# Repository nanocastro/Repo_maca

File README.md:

# Hemos trasladado el repositorio a https://gitlab.com/nanocastro/Repo_maca
# MACA
## Monitor Abierto de Calidad de Aire

**Prototipo desarrollado por el Laboratorio de Análisis Quimico y Laboratorio de Análisis Instrumental de la DETI
Facultad de Ingeniería - Universidad Nacional de Cuyo**

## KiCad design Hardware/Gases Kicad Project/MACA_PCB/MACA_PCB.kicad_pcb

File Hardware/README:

# README
Please refer to "MACA PCB Description.pdf" file when assembly.
There are two wired jumpers marked (with red circles and lines) that connect the voltage supply net.

For gases concentration measurement:
The latest schematic is the one named "MACA Esquematico.pdf", this schematic has been made in kicad due 
to file corruption of the previous ones (made with proteus). The new pcb board is not yet finished (at 15th May) 
but contains the same circuits and components as the previous PCB.  

For particle measurent:
There is a kicad project for an arduino mega 2560 shield that hosts several particle sensors and logs their measurement: 
 - SDS011 
 - PLantower S7003 
 - Shinyei PPD42

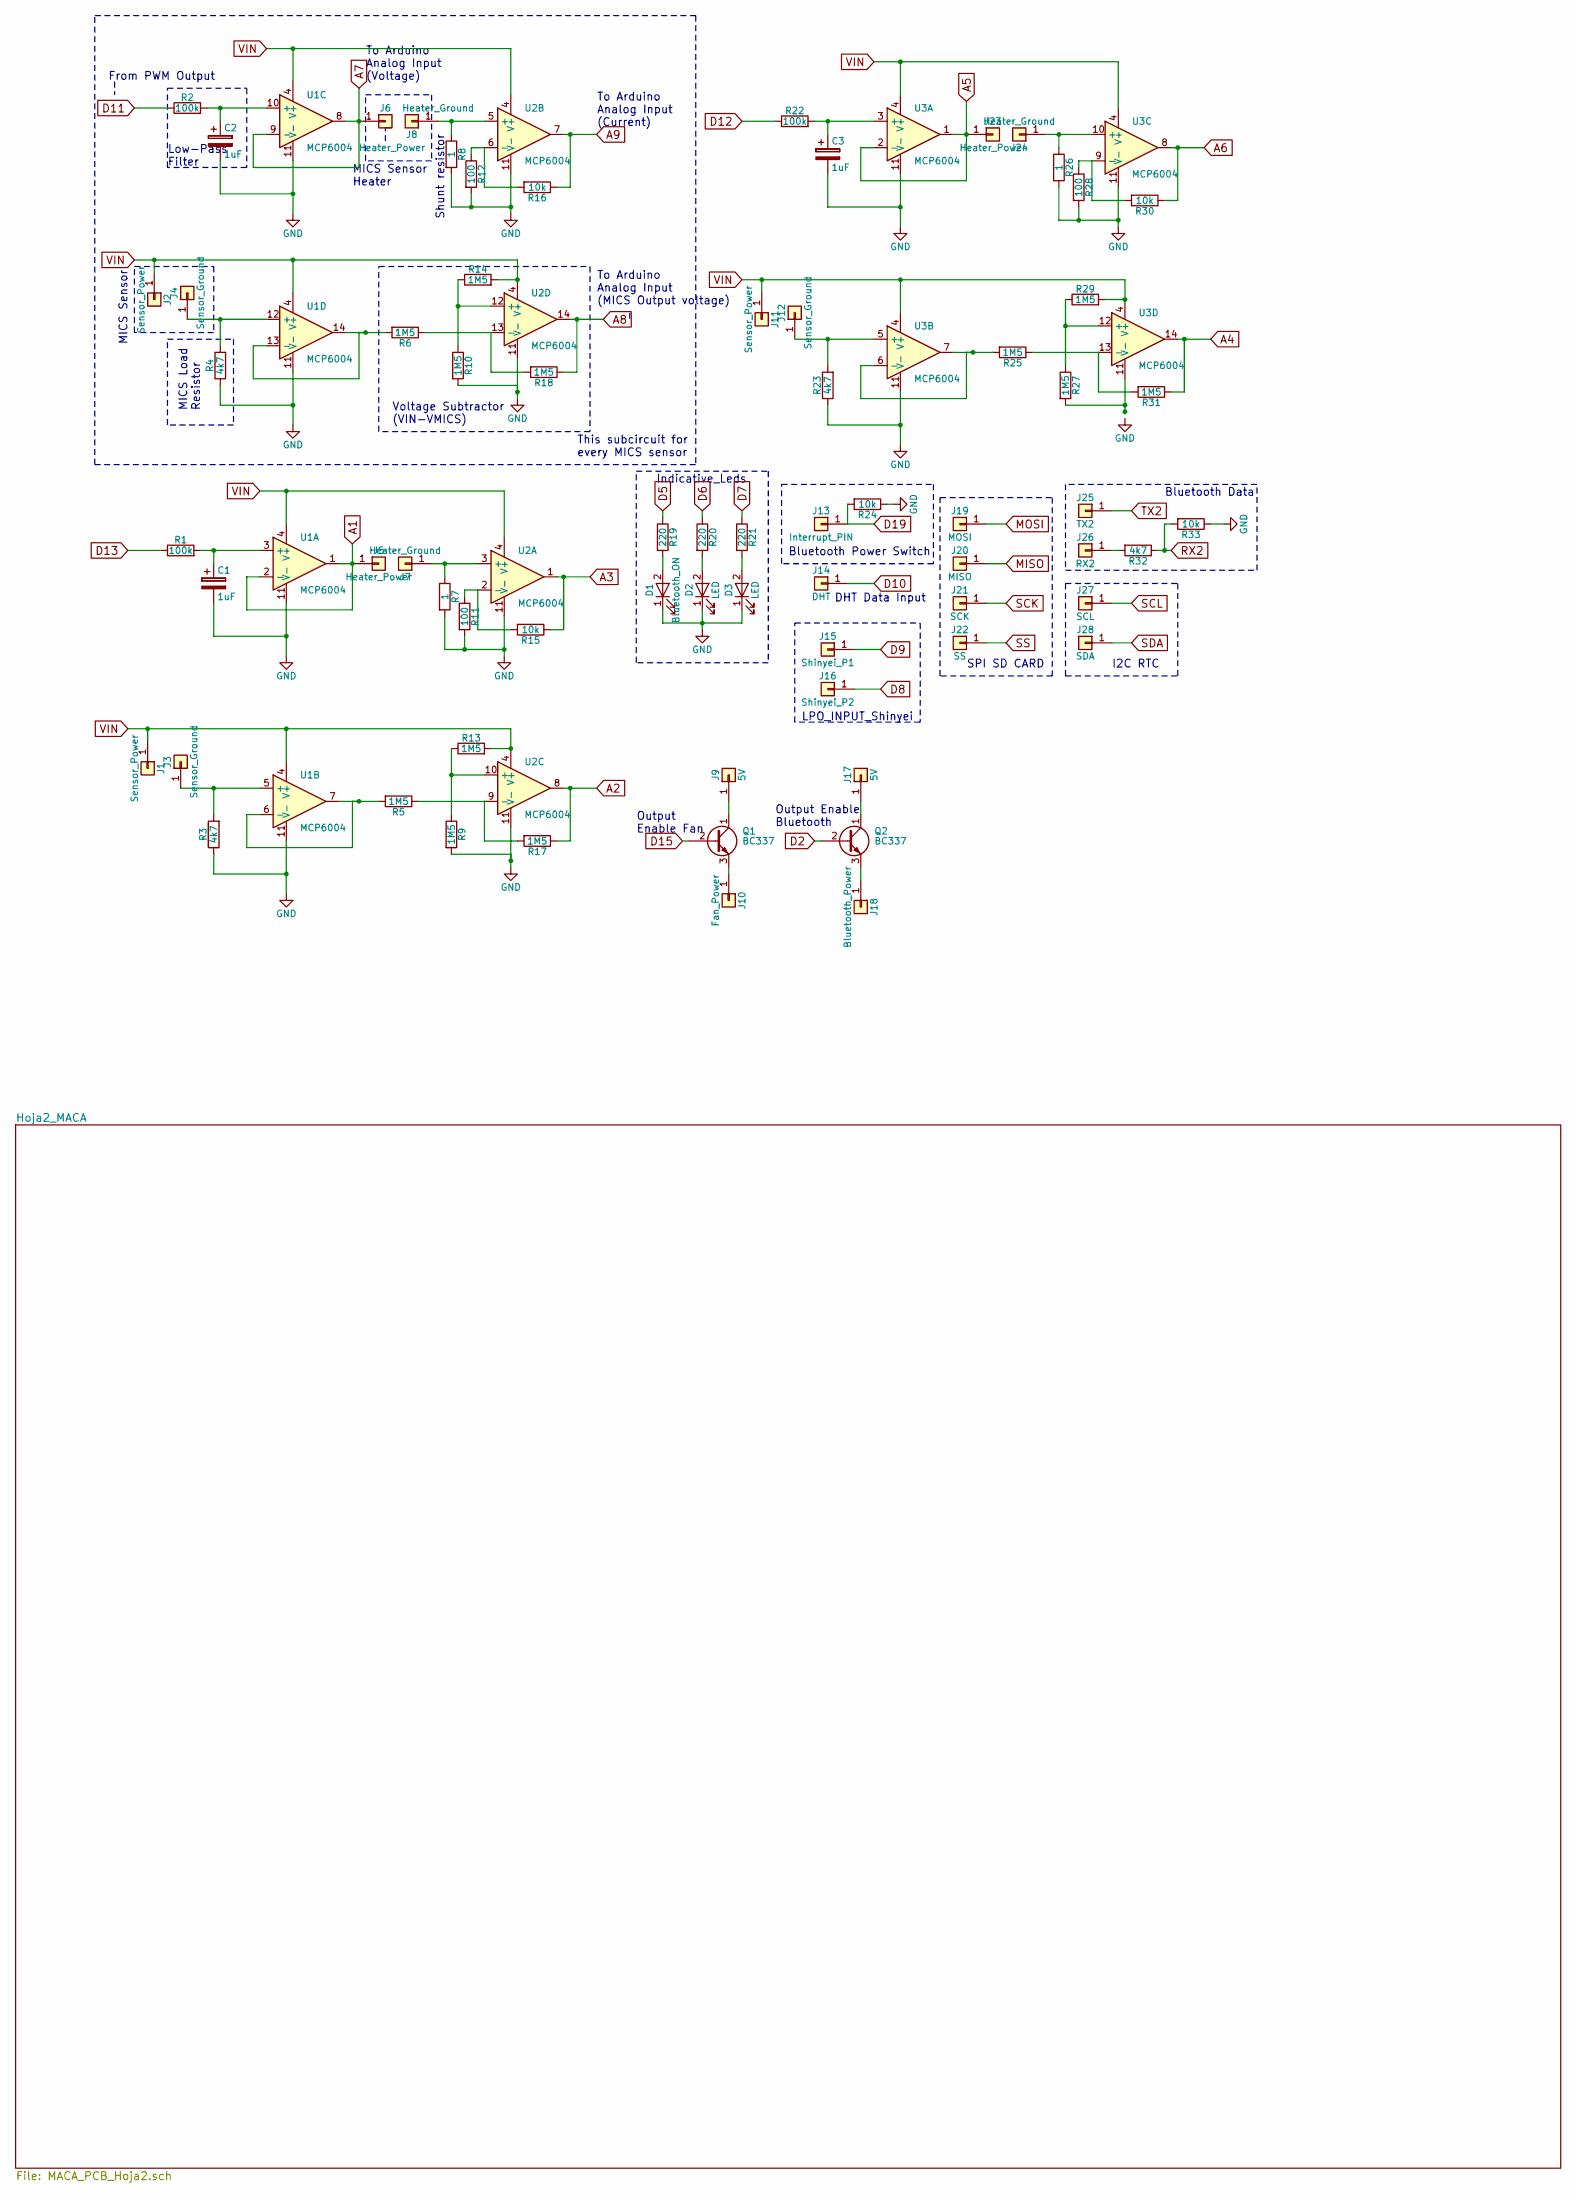
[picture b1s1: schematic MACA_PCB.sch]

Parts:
C1, C2, C3: 1uF; CP_Radial_D5.0mm_P2.50mm
D1: Bluetooth_ON; LED_D5.0mm
D2, D3: LED; LED_D5.0mm
J1, J2, J11: Sensor_Power; Pin_Header_Straight_1x01_Pitch2.54mm
J3, J4, J12: Sensor_Ground; Pin_Header_Straight_1x01_Pitch2.54mm
J5, J6, J23: Heater_Power; Pin_Header_Straight_1x01_Pitch2.54mm
J7, J8, J24: Heater_Ground; Pin_Header_Straight_1x01_Pitch2.54mm
J9, J17: 5V; Pin_Header_Straight_1x01_Pitch2.54mm
J10: Fan_Power; Pin_Header_Straight_1x01_Pitch2.54mm
J13: Interrupt_PIN; Pin_Header_Straight_1x01_Pitch2.54mm
J14: DHT; Pin_Header_Straight_1x01_Pitch2.54mm
J15: Shinyei_P1; Pin_Header_Straight_1x01_Pitch2.54mm
J16: Shinyei_P2; Pin_Header_Straight_1x01_Pitch2.54mm
J18: Bluetooth_Power; Pin_Header_Straight_1x01_Pitch2.54mm
J19: MOSI; Pin_Header_Straight_1x01_Pitch2.54mm
J20: MISO; Pin_Header_Straight_1x01_Pitch2.54mm
J21: SCK; Pin_Header_Straight_1x01_Pitch2.54mm
J22: SS; Pin_Header_Straight_1x01_Pitch2.54mm
J25: TX2; Pin_Header_Straight_1x01_Pitch2.54mm
J26: RX2; Pin_Header_Straight_1x01_Pitch2.54mm
J27: SCL; Pin_Header_Straight_1x01_Pitch2.54mm
J28: SDA; Pin_Header_Straight_1x01_Pitch2.54mm
Q1, Q2: BC337; TO-92_Molded_Narrow
R1, R2, R22: 100k; R_Axial_DIN0204_L3.6mm_D1.6mm_P7.62mm_Horizontal
R3, R4, R23, R32: 4k7; R_Axial_DIN0204_L3.6mm_D1.6mm_P7.62mm_Horizontal
R5, R6, R9, R10, R13, R14, R17, R18, R25, R27, R29, R31: 1M5; R_Axial_DIN0204_L3.6mm_D1.6mm_P7.62mm_Horizontal
R7, R8, R26: 1; R_Axial_DIN0204_L3.6mm_D1.6mm_P7.62mm_Horizontal
R11, R12, R28: 100; R_Axial_DIN0204_L3.6mm_D1.6mm_P7.62mm_Horizontal
R15, R16, R24, R30, R33: 10k; R_Axial_DIN0204_L3.6mm_D1.6mm_P7.62mm_Horizontal
R19, R20, R21: 220; R_Axial_DIN0204_L3.6mm_D1.6mm_P7.62mm_Horizontal
U1, U2, U3: MCP6004; DIP-14_W7.62mm

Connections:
A1: J5.1, U1.1, U1.2 (-); also elsewhere on the board
A3: R15.1, U2.1; also elsewhere on the board
A4: R31.1, U3.14; also elsewhere on the board
A5: J23.1, U3.1, U3.2 (-); also elsewhere on the board
A6: R30.1, U3.8; also elsewhere on the board
A7: J6.1, U1.8, U1.9 (-); also elsewhere on the board
A8: R18.1, U2.14; also elsewhere on the board
A9: R16.1, U2.7; also elsewhere on the board
D2: Q2.2 (B); also elsewhere on the board
D5: R19.1; also elsewhere on the board
D6: R20.1; also elsewhere on the board
D7: R21.1; also elsewhere on the board
D8: J16.1; also elsewhere on the board
D9: J15.1; also elsewhere on the board
D10: J14.1; also elsewhere on the board
D11: R2.1; also elsewhere on the board
D12: R22.1; also elsewhere on the board
D13: R1.1; also elsewhere on the board
D15: Q1.2 (B); also elsewhere on the board
D19: J13.1, R24.2; also elsewhere on the board
MISO: J20.1; also elsewhere on the board
MOSI: J19.1; also elsewhere on the board
unnamed: C1.1, R1.2, U1.3 (+)
unnamed: C2.1, R2.2, U1.10 (+)
unnamed: C3.1, R22.2, U3.3 (+)
unnamed: D1.2 (A), R19.2
unnamed: D2.2 (A), R20.2
unnamed: D3.2 (A), R21.2
unnamed: J3.1, R3.2, U1.5 (+)
unnamed: J4.1, R4.2, U1.12 (+)
unnamed: J7.1, R7.1, U2.3 (+)
unnamed: J8.1, R8.1, U2.5 (+)
unnamed: J9.1, Q1.1 (C)
unnamed: J10.1, Q1.3 (E)
unnamed: J12.1, R23.2, U3.5 (+)
unnamed: J17.1, Q2.1 (C)
unnamed: J18.1, Q2.3 (E)
unnamed: J24.1, R26.1, U3.10 (+)
unnamed: J26.1, R32.2
unnamed: R5.2, U1.6 (-), U1.7
unnamed: R6.2, U1.13 (-), U1.14
unnamed: R10.1, R14.1, U2.12 (+)
unnamed: R11.1, R15.2, U2.2 (-)
unnamed: R12.1, R16.2, U2.6 (-)
unnamed: R9.1, R13.1, U2.10 (+)
unnamed: R5.1, R17.2, U2.9 (-)
unnamed: R6.1, R18.2, U2.13 (-)
unnamed: R25.1, R31.2, U3.13 (-)
unnamed: R25.2, U3.6 (-), U3.7
unnamed: R27.1, R29.1, U3.12 (+)
unnamed: R28.1, R30.2, U3.9 (-)
RX2: R32.1, R33.2; also elsewhere on the board
SCK: J21.1; also elsewhere on the board
SCL: J27.1; also elsewhere on the board
SDA: J28.1; also elsewhere on the board
SS: J22.1; also elsewhere on the board
TX2: J25.1; also elsewhere on the board

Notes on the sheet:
I2C RTC
SPI SD CARD
LPO_INPUT_Shinyei
Bluetooth Power Switch
Indicative_Leds
From PWM Output
Shunt resistor
Low-Pass Filter
MICS Load Resistor
DHT Data Input
Output Enable Fan
Output Enable Bluetooth
To Arduino Analog Input (Current)
To Arduino Analog Input (Voltage)
MICS Sensor Heater
MICS Sensor
Bluetooth Data
Voltage Subtractor (VIN-VMICS)
To Arduino Analog Input (MICS Output voltage)
This subcircuit for every MICS sensor

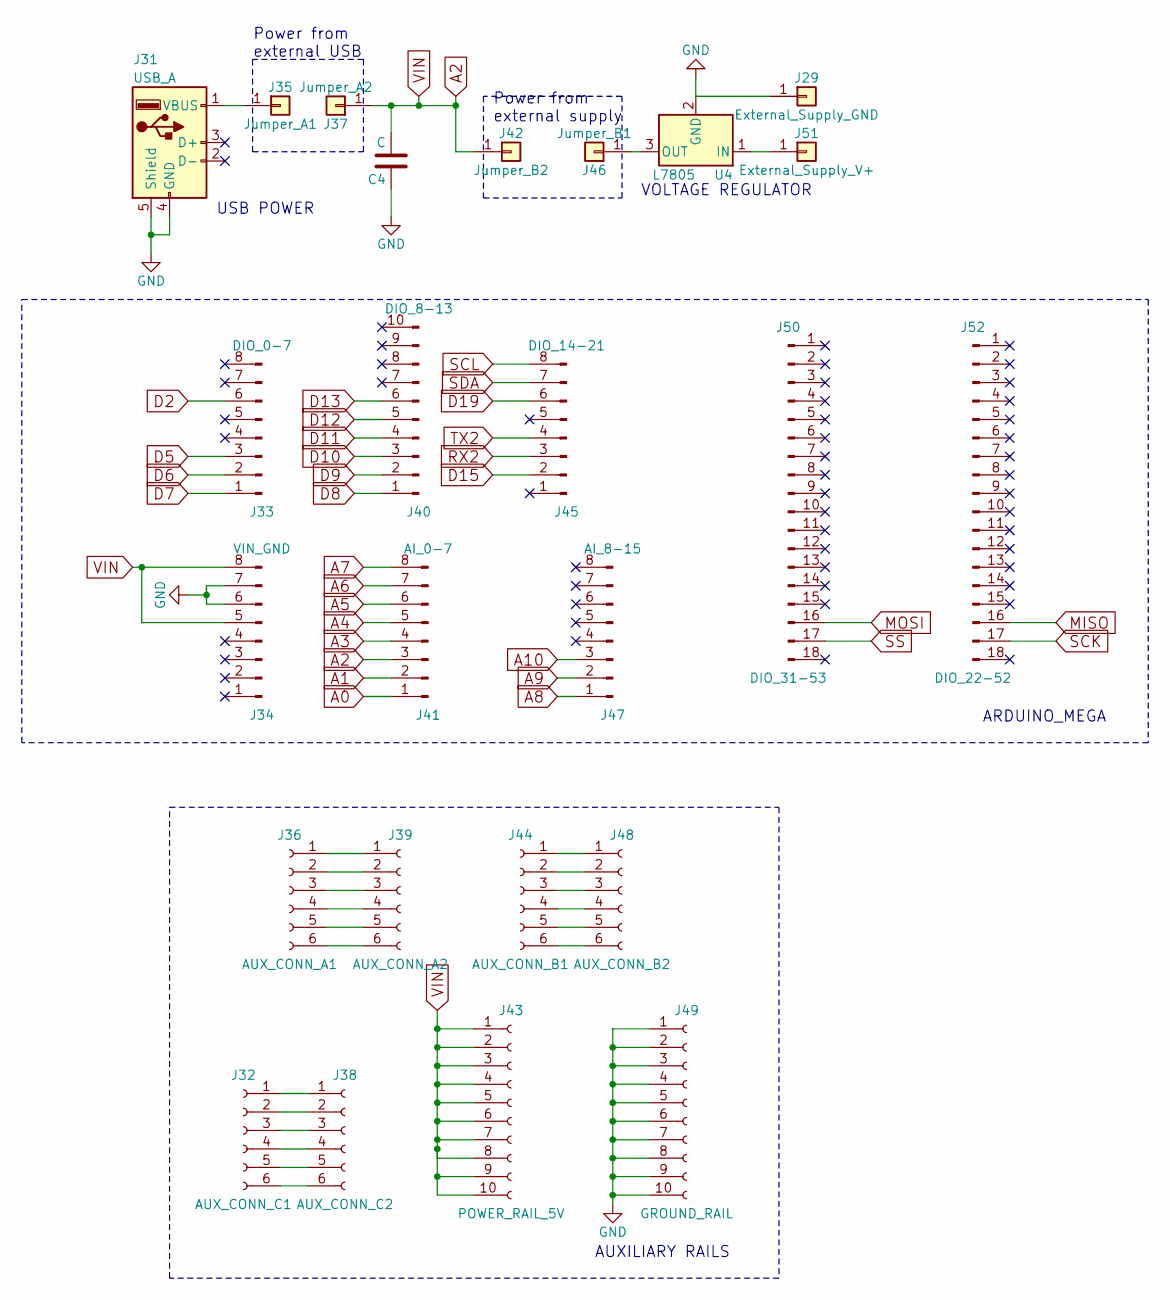
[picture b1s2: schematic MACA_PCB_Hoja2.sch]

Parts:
C4: C; C_Disc_D8.0mm_W2.5mm_P5.00mm
J29: External_Supply_GND
J31: USB_A
J32: AUX_CONN_C1; Socket_Strip_Straight_1x06_Pitch2.54mm
J33: DIO_0-7; Pin_Header_Straight_1x08_Pitch2.54mm
J34: VIN_GND; Pin_Header_Straight_1x08_Pitch2.54mm
J35: Jumper_A1; Pin_Header_Straight_1x01_Pitch2.54mm
J36: AUX_CONN_A1; Socket_Strip_Straight_1x06_Pitch2.54mm
J37: Jumper_A2; Pin_Header_Straight_1x01_Pitch2.54mm
J38: AUX_CONN_C2; Socket_Strip_Straight_1x06_Pitch2.54mm
J39: AUX_CONN_A2; Socket_Strip_Straight_1x06_Pitch2.54mm
J40: DIO_8-13; Pin_Header_Straight_1x08_Pitch2.54mm
J41: AI_0-7; Pin_Header_Straight_1x08_Pitch2.54mm
J42: Jumper_B2; Pin_Header_Straight_1x01_Pitch2.54mm
J43: POWER_RAIL_5V; Socket_Strip_Straight_1x10_Pitch2.54mm
J44: AUX_CONN_B1; Socket_Strip_Straight_1x06_Pitch2.54mm
J45: DIO_14-21; Pin_Header_Angled_1x08_Pitch2.54mm
J46: Jumper_B1; Pin_Header_Angled_1x06_Pitch2.54mm
J47: AI_8-15; Pin_Header_Angled_1x08_Pitch2.54mm
J48: AUX_CONN_B2; Socket_Strip_Straight_1x06_Pitch2.54mm
J49: GROUND_RAIL; Socket_Strip_Straight_1x10_Pitch2.54mm
J50: DIO_31-53; Pin_Header_Angled_1x18_Pitch2.54mm
J51: External_Supply_V+; Pin_Header_Angled_1x01_Pitch2.54mm
J52: DIO_22-52; Pin_Header_Straight_1x18_Pitch2.54mm
U4: L7805; TO-220-3_Vertical

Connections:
A0: J41.1
A1: J41.2; also elsewhere on the board
A3: J41.4; also elsewhere on the board
A4: J41.5; also elsewhere on the board
A5: J41.6; also elsewhere on the board
A6: J41.7; also elsewhere on the board
A7: J41.8; also elsewhere on the board
A8: J47.1; also elsewhere on the board
A9: J47.2; also elsewhere on the board
A10: J47.3
D2: J33.6; also elsewhere on the board
D5: J33.3; also elsewhere on the board
D6: J33.2; also elsewhere on the board
D7: J33.1; also elsewhere on the board
D8: J40.1; also elsewhere on the board
D9: J40.2; also elsewhere on the board
D10: J40.3; also elsewhere on the board
D11: J40.4; also elsewhere on the board
D12: J40.5; also elsewhere on the board
D13: J40.6; also elsewhere on the board
D15: J45.2; also elsewhere on the board
D19: J45.6; also elsewhere on the board
MISO: J52.16; also elsewhere on the board
MOSI: J50.16; also elsewhere on the board
unnamed: J31.1 (VBUS), J35.1
unnamed: J32.1, J38.1
unnamed: J32.2, J38.2
unnamed: J32.3, J38.3
unnamed: J32.4, J38.4
unnamed: J32.5, J38.5
unnamed: J32.6, J38.6
unnamed: J36.1, J39.1
unnamed: J36.2, J39.2
unnamed: J36.3, J39.3
unnamed: J36.4, J39.4
unnamed: J36.5, J39.5
unnamed: J36.6, J39.6
unnamed: J44.1, J48.1
unnamed: J44.2, J48.2
unnamed: J44.3, J48.3
unnamed: J44.4, J48.4
unnamed: J44.5, J48.5
unnamed: J44.6, J48.6
unnamed: J46.1, U4.3 (OUT)
unnamed: J51.1, U4.1 (IN)
RX2: J45.3; also elsewhere on the board
SCK: J52.17; also elsewhere on the board
SCL: J45.8; also elsewhere on the board
SDA: J45.7; also elsewhere on the board
SS: J50.17; also elsewhere on the board
TX2: J45.4; also elsewhere on the board

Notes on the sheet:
ARDUINO_MEGA
AUXILIARY RAILS
VOLTAGE REGULATOR
USB POWER
Power from external supply
Power from external USB

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
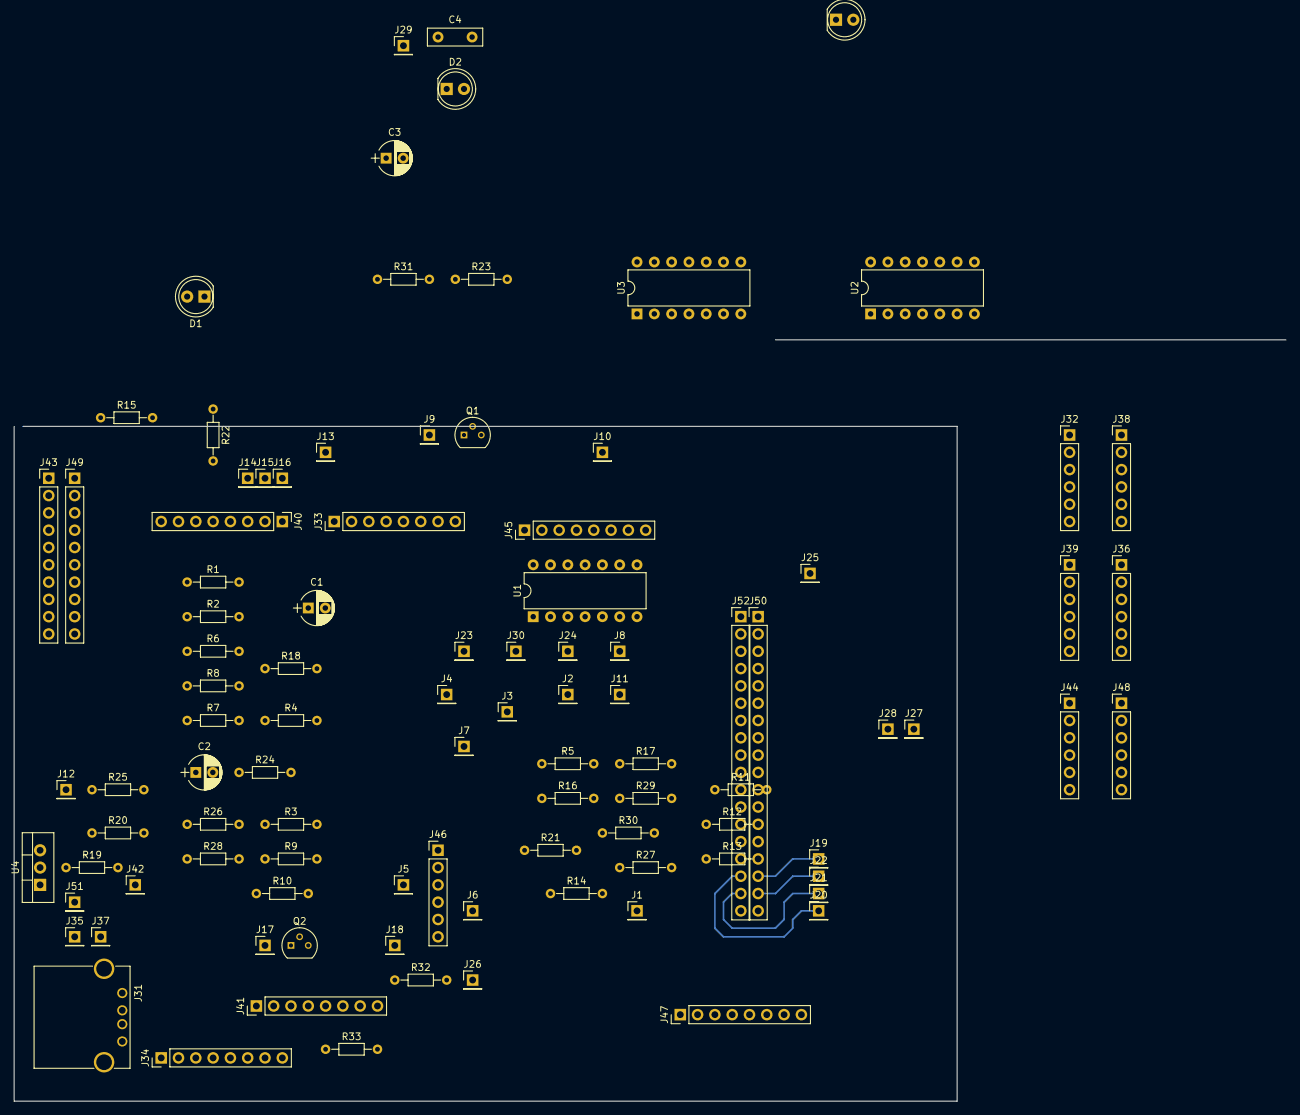
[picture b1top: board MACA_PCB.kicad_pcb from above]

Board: 2 copper layers, 186.7 x 111.8 mm, 98 parts (0 on the bottom side), 83 nets.

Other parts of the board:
J30: Conn_01x01; Pin_Header_Straight_1x01_Pitch2.54mm

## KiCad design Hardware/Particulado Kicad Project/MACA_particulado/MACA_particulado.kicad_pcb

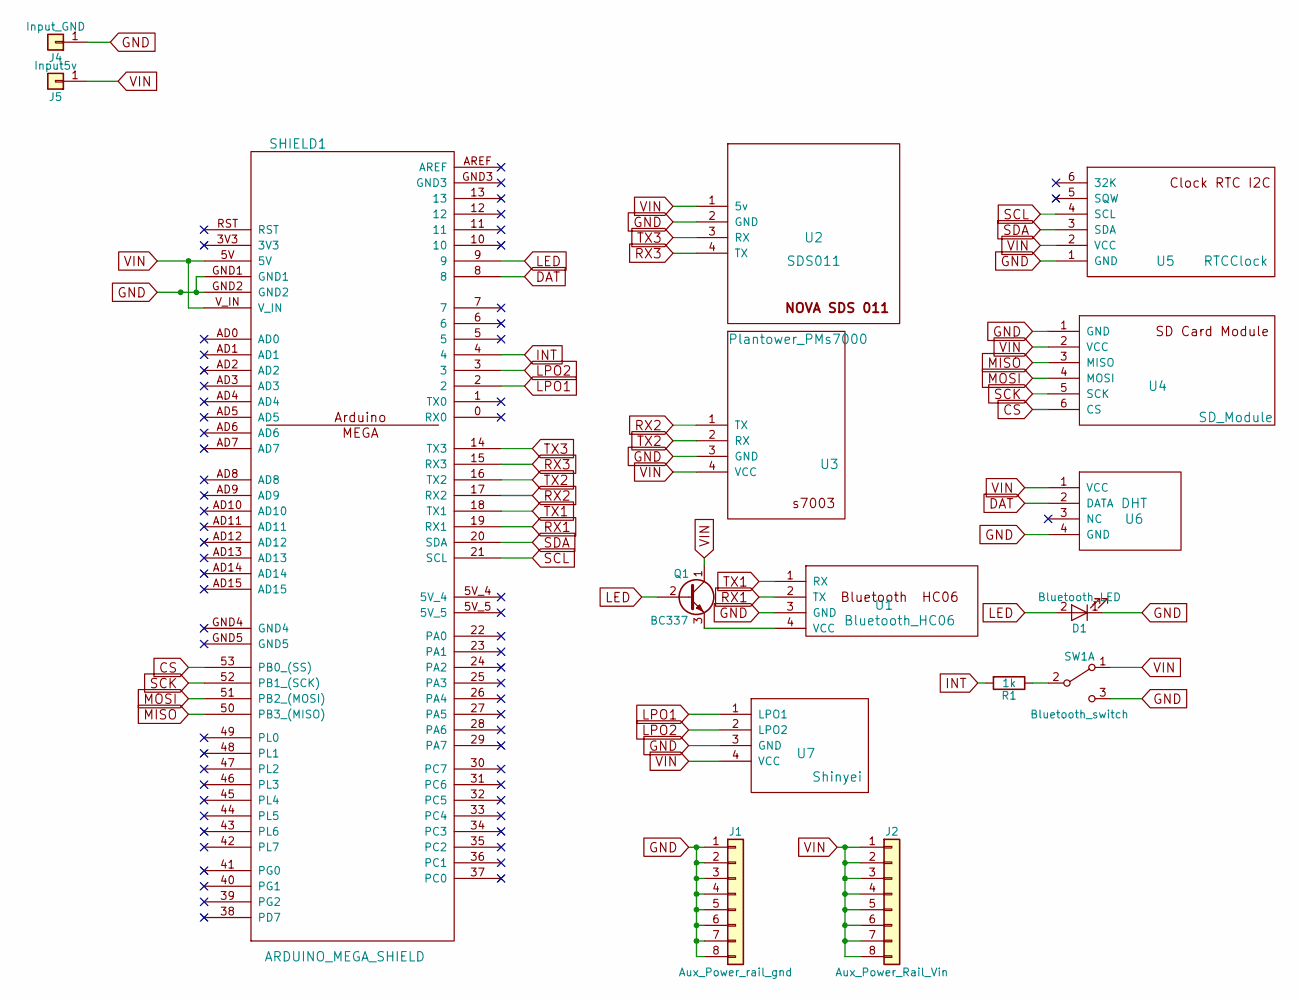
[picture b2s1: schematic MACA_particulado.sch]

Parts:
D1: Bluetooth_LED; LED_D5.0mm
J1: Aux_Power_rail_gnd; Pin_Header_Straight_1x08_Pitch2.54mm
J2: Aux_Power_Rail_Vin; Pin_Header_Straight_1x08_Pitch2.54mm
J4: Input_GND; Pin_Header_Straight_1x01_Pitch2.54mm
J5: Input5v; Pin_Header_Straight_1x01_Pitch2.54mm
Q1: BC337; TO-92_Inline_Narrow_Oval
R1: 1k; R_Axial_DIN0204_L3.6mm_D1.6mm_P7.62mm_Horizontal
SHIELD1: ARDUINO_MEGA_SHIELD; ARDUINO_MEGA_SHIELDl
SW1: Bluetooth_switch; Pin_Header_Straight_1x03_Pitch2.54mm
U1: Bluetooth_HC06; Pin_Header_Straight_1x04_Pitch2.54mm
U2: SDS011; Pin_Header_Straight_1x04_Pitch2.54mm
U3: Plantower_PMs7000; Pin_Header_Straight_1x04_Pitch2.54mm
U4: SD_Module; Pin_Header_Straight_1x06_Pitch2.54mm
U5: RTCClock; Pin_Header_Straight_1x06_Pitch2.54mm
U6: DHT; Pin_Header_Straight_1x04_Pitch2.54mm
U7: Shinyei; Pin_Header_Straight_1x04_Pitch2.54mm

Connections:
CS: SHIELD1.53 (PB0_(SS)), U4.6 (CS)
DAT: SHIELD1.8, U6.2 (DATA)
GND: D1.1 (K), J1.1, J1.2, J1.3, J1.4, J1.5, J1.6, J1.7, J1.8, J4.1, SHIELD1.GND1, SHIELD1.GND2, SW1.3 (C), U1.3 (GND), U2.2 (GND), U3.3 (GND), U4.1 (GND), U5.1 (GND), U6.4 (GND), U7.3 (GND); also elsewhere on the board
INT: R1.2, SHIELD1.4
LED: D1.2 (A), Q1.2 (B), SHIELD1.9
LPO1: SHIELD1.2, U7.1 (LPO1)
LPO2: SHIELD1.3, U7.2 (LPO2)
MISO: SHIELD1.50 (PB3_(MISO)), U4.3 (MISO)
MOSI: SHIELD1.51 (PB2_(MOSI)), U4.4 (MOSI)
unnamed: Q1.3 (E), U1.4 (VCC)
unnamed: R1.1, SW1.2 (B)
RX1: SHIELD1.19 (RX1), U1.2 (TX)
RX2: SHIELD1.17 (RX2), U3.1 (TX)
RX3: SHIELD1.15 (RX3), U2.4 (TX)
SCK: SHIELD1.52 (PB1_(SCK)), U4.5 (SCK)
SCL: SHIELD1.21 (SCL), U5.4 (SCL)
SDA: SHIELD1.20 (SDA), U5.3 (SDA)
TX1: SHIELD1.18 (TX1), U1.1 (RX)
TX2: SHIELD1.16 (TX2), U3.2 (RX)
TX3: SHIELD1.14 (TX3), U2.3 (RX)
VIN: J2.1, J2.2, J2.3, J2.4, J2.5, J2.6, J2.7, J2.8, J5.1, Q1.1 (C), SHIELD1.5V, SHIELD1.V_IN, SW1.1 (A), U2.1 (5v), U3.4 (VCC), U4.2 (VCC), U5.2 (VCC), U6.1 (VCC), U7.4 (VCC)

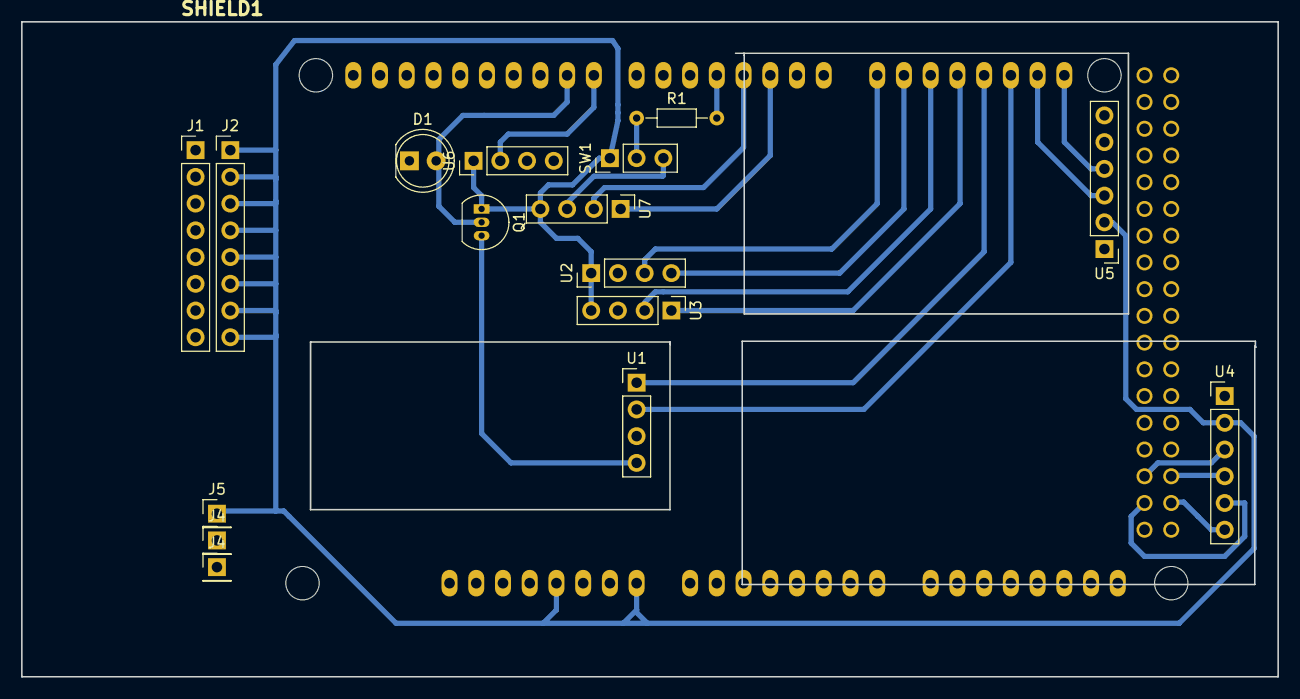
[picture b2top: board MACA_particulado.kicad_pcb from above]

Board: 2 copper layers, 119.4 x 62.2 mm, 17 parts (0 on the bottom side), 21 nets.

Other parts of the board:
J4#2: Input_GND; Pin_Header_Straight_1x01_Pitch2.54mm

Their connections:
GND: J4#2.1; also elsewhere on the board

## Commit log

2018-05-05 algunas referencias mas
2018-05-08 orden de carpetas
2018-05-08 reemplazo ; por , en archivos .csv
2018-05-08 subo datos con formato uniforme
2018-05-08 creo calibracion.md
2018-05-09 métodos calibración según Spinelle et al. 2015
2018-05-09 mas referencias y ya basta
2018-05-15 ref piedrahita
2018-05-15 mas refs
2018-05-15 agrego otras ref de calibracion
2018-05-15 ref ciencia ciudadana
2018-05-15 empiezo analisis PM
2018-05-22 ref HackAir
2018-05-22 borro ref duplicadas
